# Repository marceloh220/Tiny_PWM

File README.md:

# Tiny_PWM
Dual channel PWM driver controller. For LEDs, motors and other strangers things.\
Based on Attiny25/45/85 microcontroller this device have two PWM channels controlled by independent potentiometer.

Fusebits:
  - Low:      0x62
  - High:     0xDC
  - Extended: 0xFF

Install avr-gcc:

 - windows:
    
       https://blog.zakkemble.net/avr-gcc-builds/
    
   Include the bin directory on system path
    
 -  Debian/Ubuntu:
    
        sudo apt install gcc-avr avr-libc binutils-avr
   
  - RedHat/Fedora:
    
        sudo dnf install avr-gcc avr-libc avr-binutils
    
  - Arch/Manjaro:
    
        sudo pacman -S avr-gcc avr-libc avr-binutils

Install avrdude:

  - Windows:

    Avrdude comes with avr-gcc
   
  - Debian/Ubuntu:
    
        sudo apt install avrdude
   
  - RedHat/Fedora:
    
        sudo dnf install avrdude
    
  - Arch/Manjaro:
    
        sudo pacman -S avrdude

Install Make:
    
  - Windows:
   
    Make comes with avr-gcc
    
   - Debian/Ubuntu:
   
    sudo apt install make
   
   - RedHat/Fedora:
   
    sudo dnf install make
   
   - Arch/Manjaro:
   
    sudo pacman -S make

Using:
  
   - Generate executable .elf files
     
         make all
         
   - Generate .hex files
   
         make hex
   
   - Clean build
        
         make clean
         
   - Verify size program
   
         make size
     
   - Configure fusebits
       
         make fuses
       
   - Upload to device

         make program

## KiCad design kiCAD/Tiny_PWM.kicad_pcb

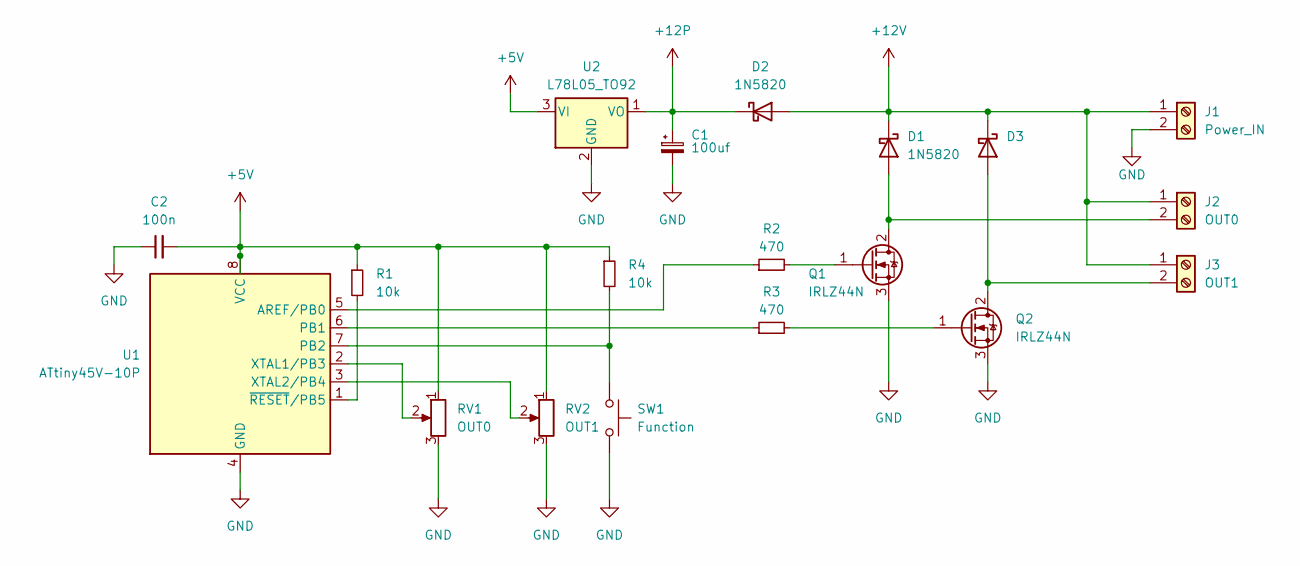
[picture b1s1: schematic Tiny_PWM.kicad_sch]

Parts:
C1: 100uf; CP_Radial_D6.3mm_P2.50mm
C2: 100n; C_Disc_D5.0mm_W2.5mm_P2.50mm
D1, D2, D3: 1N5820; D_DO-34_SOD68_P7.62mm_Horizontal
J1: Power_IN; TerminalBlock_Altech_AK300-2_P5.00mm
J2: OUT0; TerminalBlock_Altech_AK300-2_P5.00mm
J3: OUT1; TerminalBlock_Altech_AK300-2_P5.00mm
Q1, Q2: IRLZ44N; TO-220-3_Vertical
R1, R4: 10k; R_Axial_DIN0204_L3.6mm_D1.6mm_P7.62mm_Horizontal
R2, R3: 470; R_Axial_DIN0204_L3.6mm_D1.6mm_P7.62mm_Horizontal
RV1: OUT0; Potentiometer_Alps_RK163_Single_Horizontal
RV2: OUT1; Potentiometer_Alps_RK163_Single_Horizontal
SW1: Function; SW_PUSH_6mm
U1: ATtiny45V-10P; DIP-8_W7.62mm
U2: L78L05_TO92; TO-92_Inline

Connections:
+5V: C2.2, R1.1, R4.1, RV1.1, RV2.1, U1.8 (VCC), U2.3 (VI)
+12P: C1.1, D2.1 (K), U2.1 (VO)
+12V: D1.1 (K), D2.2 (A), D3.1 (K), J1.1, J2.1, J3.1
GND: C1.2, C2.1, J1.2, Q1.3 (S), Q2.3 (S), RV1.3, RV2.3, SW1.2, U1.4 (GND), U2.2 (GND)
unnamed: D1.2 (A), J2.2, Q1.2 (D)
unnamed: D3.2 (A), J3.2, Q2.2 (D)
unnamed: Q1.1 (G), R2.2
unnamed: Q2.1 (G), R3.2
unnamed: R2.1, U1.5 (AREF/PB0)
unnamed: R3.1, U1.6 (PB1)
unnamed: R4.2, SW1.1, U1.7 (PB2)
unnamed: RV1.2, U1.2 (XTAL1/PB3)
unnamed: RV2.2, U1.3 (XTAL2/PB4)
unnamed: R1.2, U1.1 (~RESET/PB5)

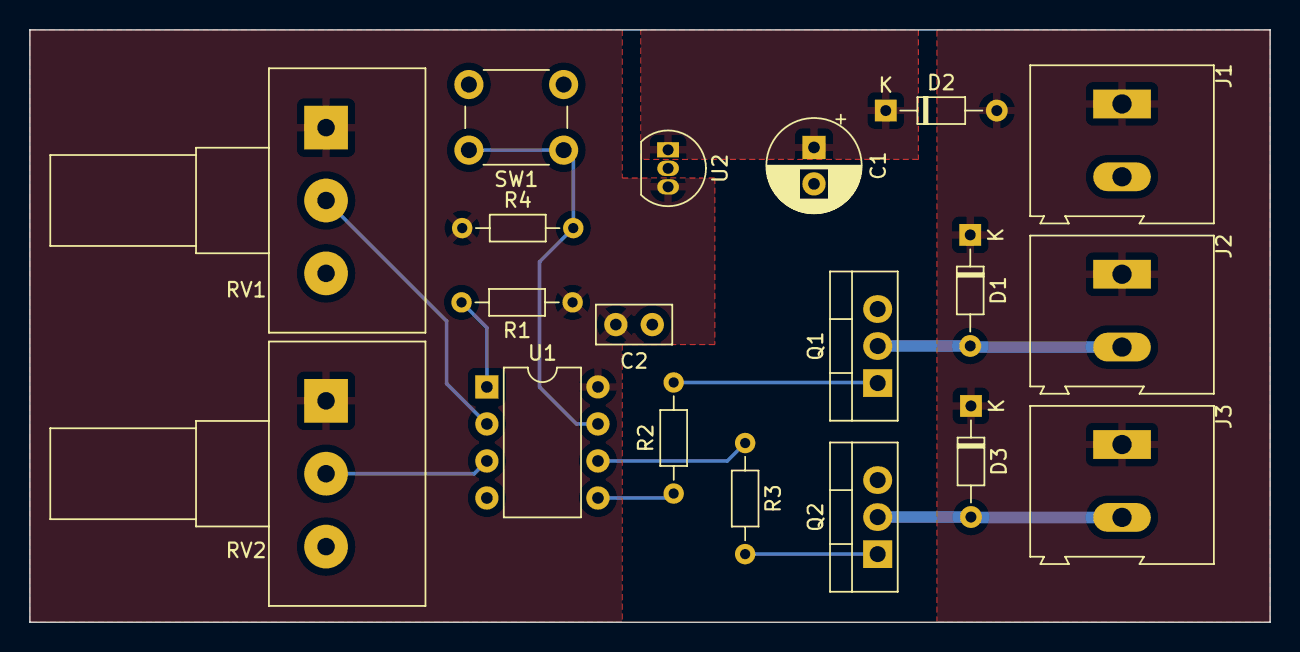
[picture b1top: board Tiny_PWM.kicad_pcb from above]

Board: 2 copper layers, 85.1 x 40.6 mm, 19 parts (0 on the bottom side), 14 nets.

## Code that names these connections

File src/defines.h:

/*
	defines.h

	MIT License

	Copyright (c) 2022 Marcelo H Moraes

	Permission is hereby granted, free of charge, to any person obtaining a copy
	of this software and associated documentation files (the "Software"), to deal
	in the Software without restriction, including without limitation the rights
	to use, copy, modify, merge, publish, distribute, sublicense, and/or sell
	copies of the Software, and to permit persons to whom the Software is
	furnished to do so, subject to the following conditions:

	The above copyright notice and this permission notice shall be included in all
	copies or substantial portions of the Software.

	THE SOFTWARE IS PROVIDED "AS IS", WITHOUT WARRANTY OF ANY KIND, EXPRESS OR
	IMPLIED, INCLUDING BUT NOT LIMITED TO THE WARRANTIES OF MERCHANTABILITY,
	FITNESS FOR A PARTICULAR PURPOSE AND NONINFRINGEMENT. IN NO EVENT SHALL THE
	AUTHORS OR COPYRIGHT HOLDERS BE LIABLE FOR ANY CLAIM, DAMAGES OR OTHER
	LIABILITY, WHETHER IN AN ACTION OF CONTRACT, TORT OR OTHERWISE, ARISING FROM,
	OUT OF OR IN CONNECTION WITH THE SOFTWARE OR THE USE OR OTHER DEALINGS IN THE
	SOFTWARE.

	Description:
		Are two channels of PWM control output, each one controlled by a potentiometer
		Are three modes:
			mode 0: The MCU is in power down and outputs is turn off
  			mode 1: Only OUT0 is driven, the OUT1 is turn off
  			mode 2: Only OUT1 is driven, the OUT0 is turn off
  			mode 3(default): Both outputs is driven
  	
  	Identity of system:
  		OUT1: PWM out 0 at PB0 pin
  		OUT2: PWM out 1 at PB1 pin
  		POT1: ADC channel 2 control PWM out at PB4 pin
  		POT2: ADC channel 3 control PWM out at PB3 pin
  		BTN0: INT0 interrupt to wakeup MCU and change modes
  		
  	Peripheral:
  		The clock MCU is running at 1MHz
  		The Brown-down detect programed at 4.5V
  		The PWM is generated by Timer 0 at frequency predefined and calculate by move average with number max of samples defined in NUMBER_OF_SAMPLES
  		Timer 1 generate the times to read the analog inputs with ADC each 16ms and debounce the button at 114ms
  		The ADC read two analog inputs, the ADC complete ISR change between the two channels, each channel have frequency 30 samples/s 
  		The button is read at falling edge by external interrupt INT0, a debounce time of 114ms verify if button is liberated.
  		INT0 wakeup CPU from power down and change PWM mode
        	Sleep Power Down is active in mode 0
  		Sleep IDLE is active in the end of each ADC read, sample process and control read, until the next ADC read time
  
*/
#ifndef DEFINES_H_
#define DEFINES_H_

#include "avr/io.h"
#include "avr/eeprom.h"
#include "avr/interrupt.h"
#include "avr/sleep.h"
#include "avr/wdt.h"
#include "util/delay.h"
#include "inttypes.h"

/****                    Pins configuration                   ****/

#define _OUT0 PB0
#define _OUT1 PB1

#define _OUT0_PWM OCR0A
#define _OUT1_PWM OCR0B

#define _BT	PB2

//#define	BUTTON_ENABLE
//#define	AUTO_TEST
//#define DUAL_CHANNEL

#define _ADC_CH0	2
#define _ADC_CH1	3

/****                    Filter configuration                    ****/

/*	Number of samples in moving average
	More samples means steady and smooth captures, but slower the changes*/
#define NUMBER_OF_SAMPLES		10

// Threshold to PWM out accept variation
#define PWM_OUT_THRESHOLD		5

/****                    PWM configuration                    ****/

/*
	Fclk = 1MHz
	
	PWM Correct Phase mode:
		Fpwm = Fclk / N / 510
		
	PWM Fast mode:
		Fpwm = Fclk / N / 256
	
	Above 300Hz is good for the eyes, but to camera captures needs above 1KHz
	Controlled led must match frequency, using more speed may result in loss of control resolution
	
	Select one mode and prescaler below
	
	Default mode:
		Fpwm = 1E6 / 1 / 510 = 1960 Hz
	
*/

#define PWM_MODE	(_bv(WGM00))				/*Phase Correct PWM*/
//#define PWM_MODE	(_bv(WGM01)|_bv(WGM00))		/*Fast PWM*/

#define PWM_PRESCALE (_bv(CS00))				/*Fclk/1, N = 1*/
//#define PWM_PRESCALE (_bv(CS01))				/*Fclk/8, N = 8 */
//#define PWM_PRESCALE (_bv(CS01)|_bv(CS00))	/*Fclk/64, N = 64*/
//#define PWM_PRESCALE (_bv(CS02))				/*Fclk/256, N = 256*/
//#define PWM_PRESCALE (_bv(CS02)|_bv(CS00))	/*Fclk/1024, N = 1024*/

/****                    Utils Macros                    ****/

#define _bv(_bit)	(1<<_bit)

#define _out(_pin)		{PORTB&=~_bv(_pin); DDRB|=_bv(_pin);}
#define _pullup(_pin)	{DDRB&=~_bv(_pin); PORTB|=_bv(_pin);}

#define _off(_pin)	(PORTB&=~_bv(_pin))
#define _on(_pin)	(PORTB|=_bv(_pin))

#define _read(_pin)	(PINB&_bv(_pin))

#define system_init() {sei();}

#endif /* DEFINES_H_ */

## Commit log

2022-08-12 Beta version 0.2
2022-08-13 Beta 1.02
    Added Makefile and comments documentation
2022-08-14 Add flyback diodes on outputs
2022-08-14 Added more modes to PWM out
    Added PWM PWM Fast and PWM Correct Phase modes
    Frequency output can be calculated using these modes and prescalers
2022-08-14 Added Makefile for windows support
    Makefile for Linux and Windows
2022-08-14 Added user's manual for Linux and Windows
2022-08-14 Correct Makefile for Windows
2022-08-15 Update README.md
    Theres no need to instal make in windows, it's comes with avr-gcc instalation. Only put the bin directory in system path.
2022-08-16 Makefile for Windows and Linux
2022-08-16 Unified Makefile for Linux and Windows
2022-08-19 Release 1.0.2
    Added license program and release after final tests
2023-08-05 kiCAD
    Add schematics and PCI layout with KiCad
2023-10-09 New output filter
    An added output filter method to prevent flickering.
